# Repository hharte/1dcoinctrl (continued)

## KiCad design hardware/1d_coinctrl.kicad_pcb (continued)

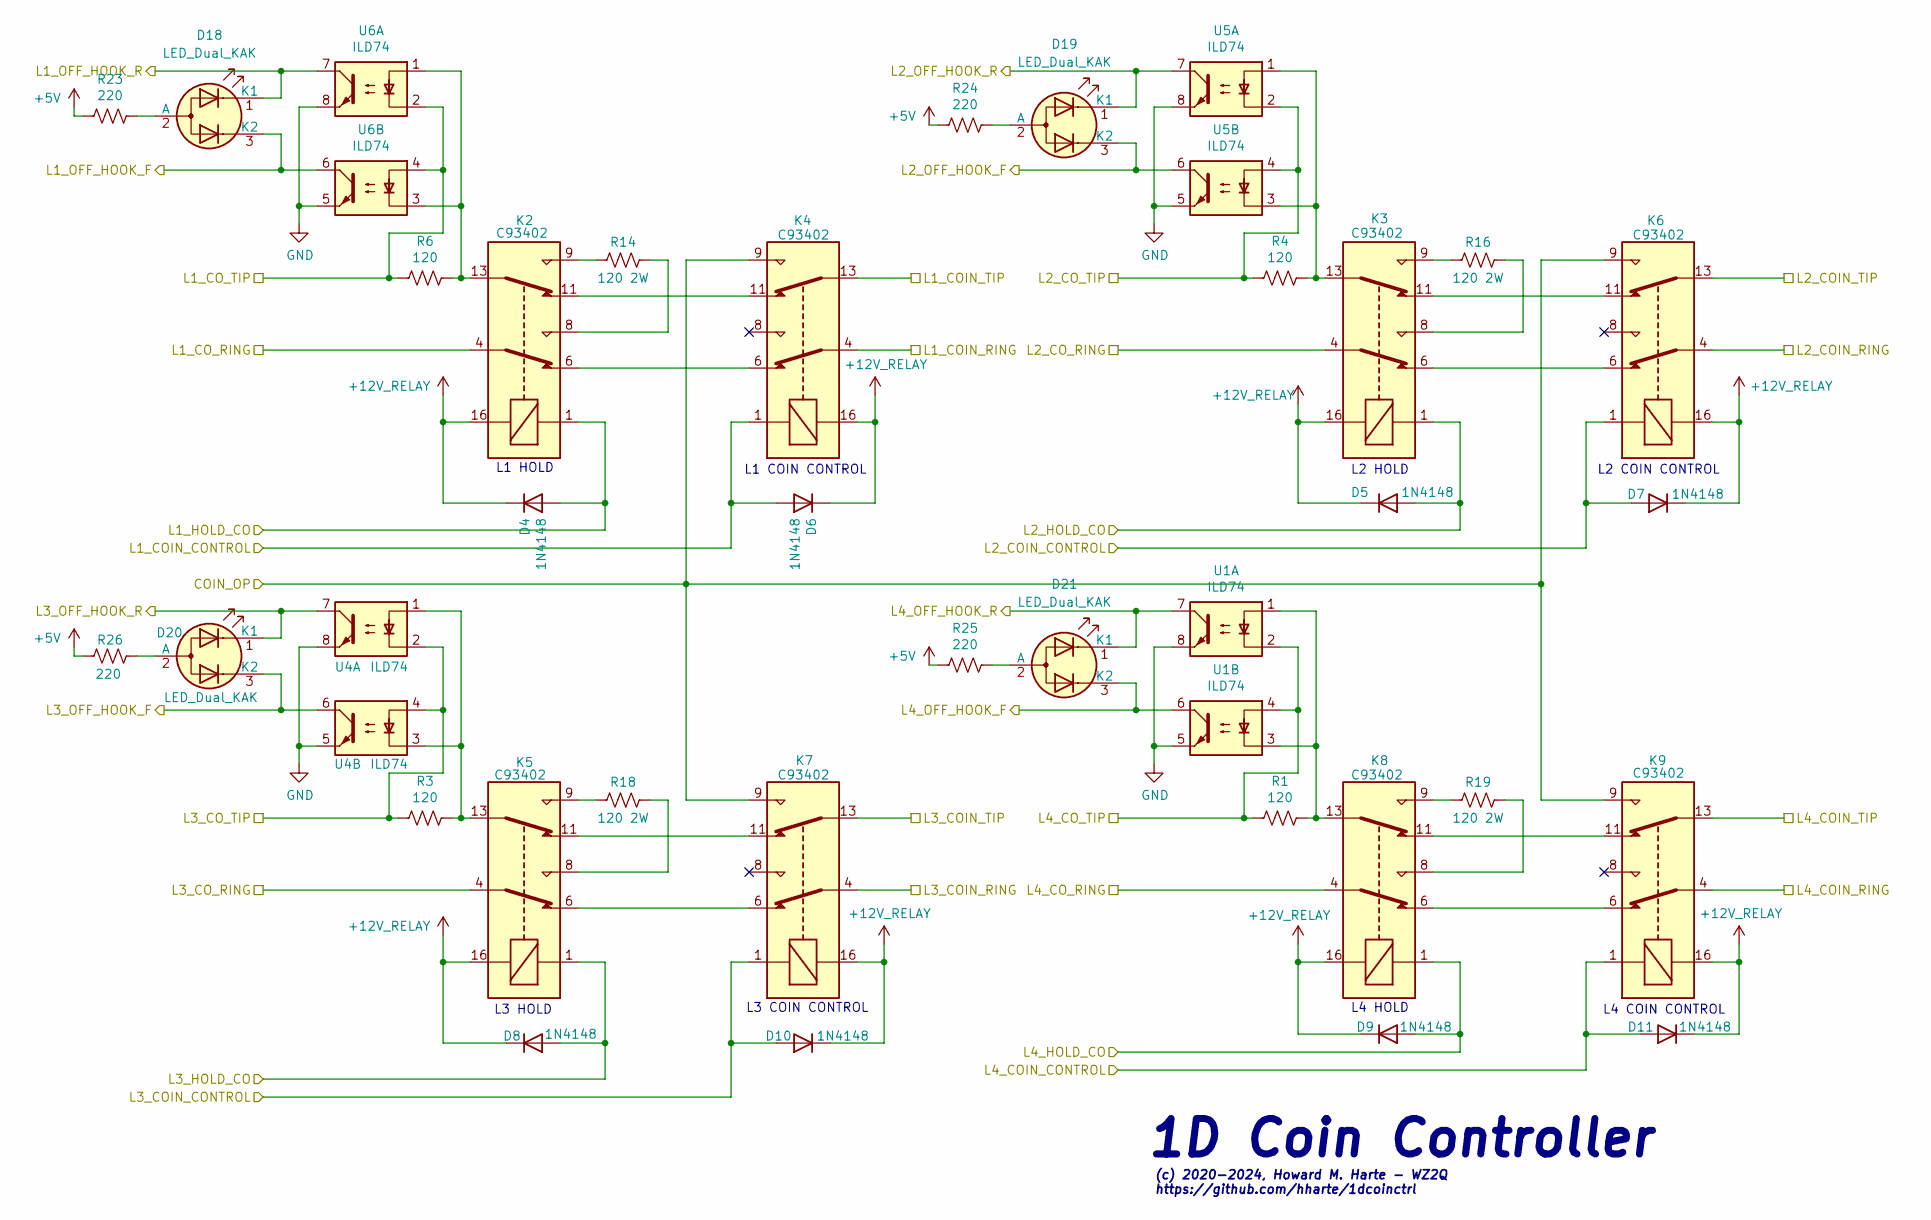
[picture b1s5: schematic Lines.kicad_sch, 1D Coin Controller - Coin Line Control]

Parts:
D4, D5, D6, D7, D8, D9, D10, D11: 1N4148; D_DO-35_SOD27_P7.62mm_Horizontal; MPN 1N4148TA; Digi-Key_PN 1N4148TACT-ND
D18, D19, D20, D21: LED_Dual_KAK; LED_D5.0mm-3; MPN XLMDKVG59MCA; Digi-Key_PN 1497-1357-ND
K2, K3, K4, K5, K6, K7, K8, K9: C93402; Relay_DPDT_Omron_G5V-2; MPN C93402; Digi-Key_PN PB1125-ND
R1, R3, R4, R6: 120; R_Axial_DIN0207_L6.3mm_D2.5mm_P7.62mm_Horizontal; MPN CFM12JT120R; Digi-Key_PN S120HCT-ND
R14, R16, R18, R19: 120 2W; R_Axial_DIN0516_L15.5mm_D5.0mm_P20.32mm_Horizontal; MPN FMP200JR-52-120R; Digi-Key_PN 120ZCT-ND
R23, R24, R25, R26: 220; R_Axial_DIN0207_L6.3mm_D2.5mm_P7.62mm_Horizontal; MPN CFM12JT220R; Digi-Key_PN S220HCT-ND
U1, U4, U5, U6: ILD74; DIP-8_W7.62mm_Socket; MPN CNY74-2H; Digi-Key_PN CNY74-2H-ND

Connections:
+5V: R23.2, R24.2, R25.2, R26.2; also elsewhere on the board
+12V_RELAY: D4.1 (K), D5.1 (K), D6.1 (K), D7.1 (K), D8.1 (K), D9.1 (K), D10.1 (K), D11.1 (K), K2.16, K3.16, K4.16, K5.16, K6.16, K7.16, K8.16, K9.16; also elsewhere on the board
/Coin Line Control/COIN_OP: K4.9, K6.9, K7.9, K9.9; also elsewhere on the board
/Coin Line Control/L1_COIN_CONTROL: D6.2 (A), K4.1; also elsewhere on the board
/Coin Line Control/L1_HOLD_CO: D4.2 (A), K2.1; also elsewhere on the board
/Coin Line Control/L1_OFF_HOOK_F: D18.3 (K2), U6.6; also elsewhere on the board
/Coin Line Control/L1_OFF_HOOK_R: D18.1 (K1), U6.7; also elsewhere on the board
/Coin Line Control/L2_COIN_CONTROL: D7.2 (A), K6.1; also elsewhere on the board
/Coin Line Control/L2_HOLD_CO: D5.2 (A), K3.1; also elsewhere on the board
/Coin Line Control/L2_OFF_HOOK_F: D19.3 (K2), U5.6; also elsewhere on the board
/Coin Line Control/L2_OFF_HOOK_R: D19.1 (K1), U5.7; also elsewhere on the board
/Coin Line Control/L3_COIN_CONTROL: D10.2 (A), K7.1; also elsewhere on the board
/Coin Line Control/L3_HOLD_CO: D8.2 (A), K5.1; also elsewhere on the board
/Coin Line Control/L3_OFF_HOOK_F: D20.3 (K2), U4.6; also elsewhere on the board
/Coin Line Control/L3_OFF_HOOK_R: D20.1 (K1), U4.7; also elsewhere on the board
/Coin Line Control/L4_COIN_CONTROL: D11.2 (A), K9.1; also elsewhere on the board
/Coin Line Control/L4_HOLD_CO: D9.2 (A), K8.1; also elsewhere on the board
/Coin Line Control/L4_OFF_HOOK_F: D21.3 (K2), U1.6; also elsewhere on the board
/Coin Line Control/L4_OFF_HOOK_R: D21.1 (K1), U1.7; also elsewhere on the board
/L1_COIN_RING: K4.4; also elsewhere on the board
/L1_COIN_TIP: K4.13; also elsewhere on the board
/L1_CO_RING: K2.4; also elsewhere on the board
/L1_CO_TIP: R6.2, U6.2, U6.4; also elsewhere on the board
/L2_COIN_RING: K6.4; also elsewhere on the board
/L2_COIN_TIP: K6.13; also elsewhere on the board
/L2_CO_RING: K3.4; also elsewhere on the board
/L2_CO_TIP: R4.2, U5.2, U5.4; also elsewhere on the board
/L3_COIN_RING: K7.4; also elsewhere on the board
/L3_COIN_TIP: K7.13; also elsewhere on the board
/L3_CO_RING: K5.4; also elsewhere on the board
/L3_CO_TIP: R3.2, U4.2, U4.4; also elsewhere on the board
/L4_COIN_RING: K9.4; also elsewhere on the board
/L4_COIN_TIP: K9.13; also elsewhere on the board
/L4_CO_RING: K8.4; also elsewhere on the board
/L4_CO_TIP: R1.2, U1.2, U1.4; also elsewhere on the board
GND: U1.5, U1.8, U4.5, U4.8, U5.5, U5.8, U6.5, U6.8; also elsewhere on the board
unnamed: D18.2 (A), R23.1
unnamed: D19.2 (A), R24.1
unnamed: D20.2 (A), R26.1
unnamed: D21.2 (A), R25.1
unnamed: K2.6, K4.6
unnamed: K2.8, R14.1
unnamed: K2.9, R14.2
unnamed: K2.11, K4.11
unnamed: K2.13, R6.1, U6.1, U6.3
unnamed: K3.6, K6.6
unnamed: K3.8, R16.1
unnamed: K3.9, R16.2
unnamed: K3.11, K6.11
unnamed: K3.13, R4.1, U5.1, U5.3
unnamed: K5.6, K7.6
unnamed: K5.8, R18.1
unnamed: K5.9, R18.2
unnamed: K5.11, K7.11
unnamed: K5.13, R3.1, U4.1, U4.3
unnamed: K8.6, K9.6
unnamed: K8.8, R19.1
unnamed: K8.9, R19.2
unnamed: K8.11, K9.11
unnamed: K8.13, R1.1, U1.1, U1.3

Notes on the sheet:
L2 HOLD
L4 COIN CONTROL
L1 COIN CONTROL
L2 COIN CONTROL
L3 HOLD
1D Coin Controller
L1 HOLD
L3 COIN CONTROL
L4 HOLD
(c) 2020-2024, Howard M. Harte - WZ2Q https://github.com/hharte/1dcoinctrl

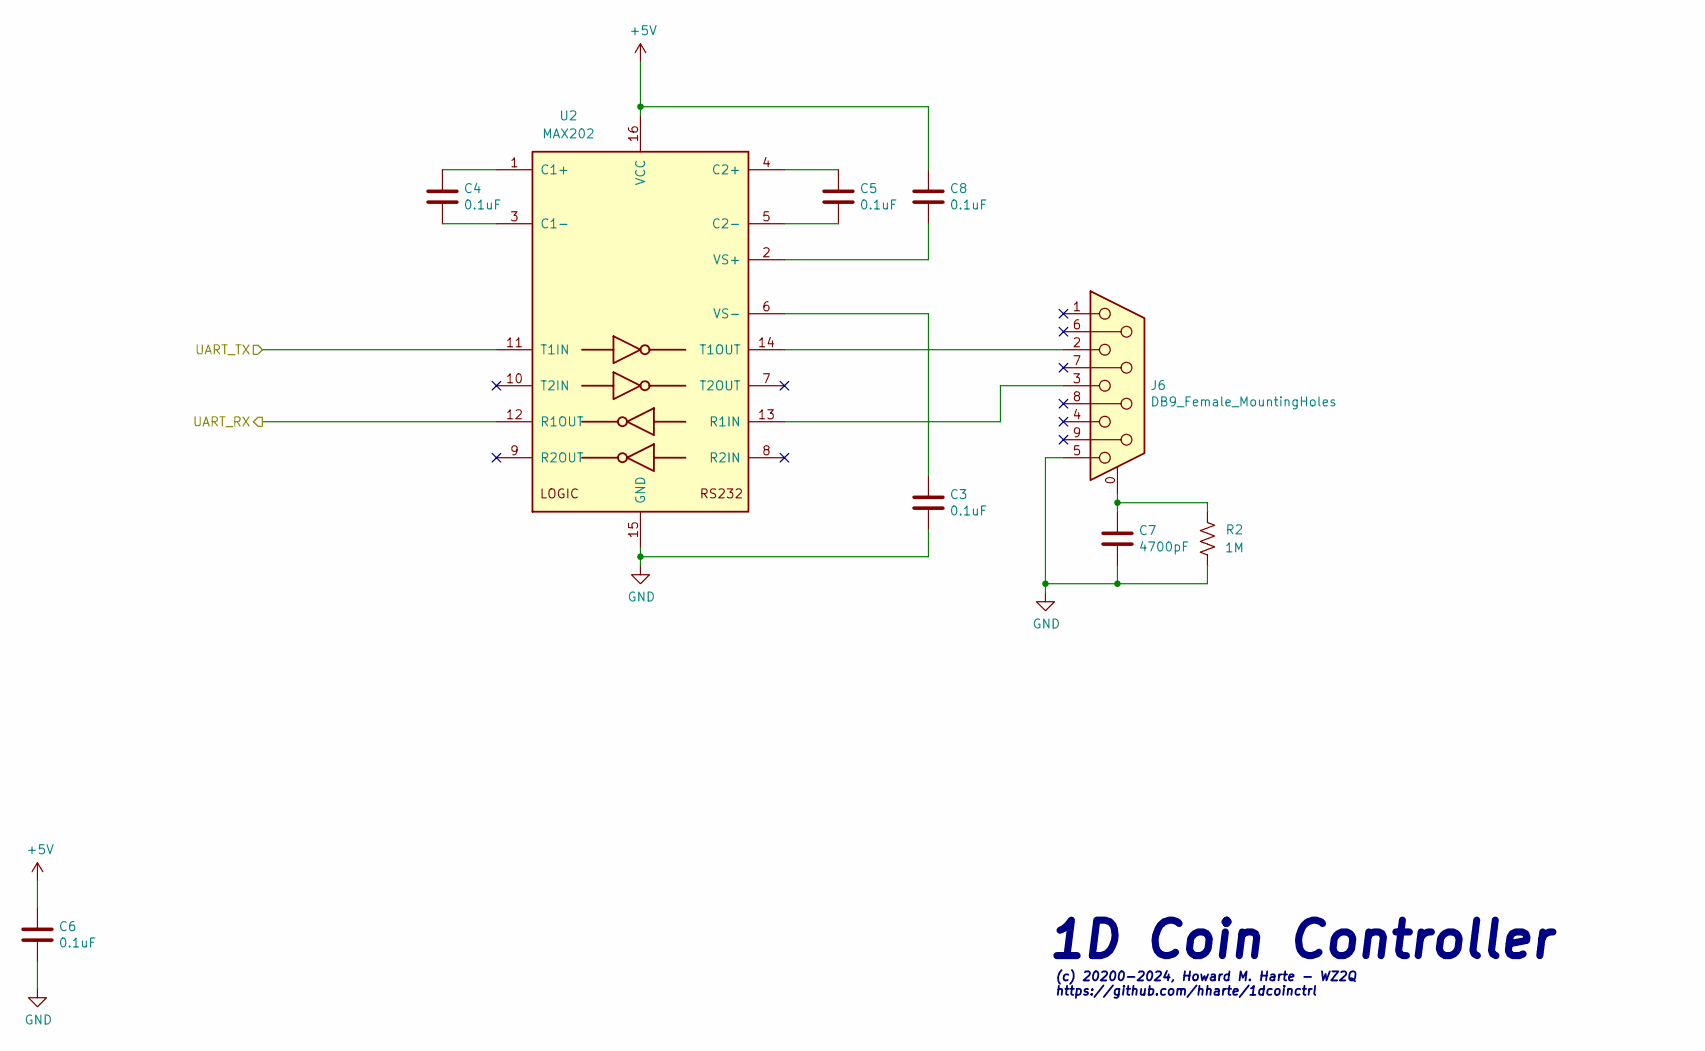
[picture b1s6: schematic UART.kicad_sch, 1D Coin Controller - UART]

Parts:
C3, C4, C5, C6, C8: 0.1uF; C_Disc_D3.0mm_W2.0mm_P2.50mm; MPN K104M15X7RF5TL2; Digi-Key_PN 56-K104M15X7RF5TL2CT-ND
C7: 4700pF; C_Disc_D4.3mm_W1.9mm_P5.00mm; MPN S472M39Z5UN63J5R; Digi-Key_PN 1288PH-ND
J6: DB9_Female_MountingHoles; DSUB-9_Female_Horizontal_P2.77x2.84mm_EdgePinOffset7.70mm_H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; MPN 747844-4; Digi-Key_PN A23303-ND
R2: 1M; R_Axial_DIN0207_L6.3mm_D2.5mm_P7.62mm_Horizontal; MPN CFM12JT1M00; Digi-Key_PN S1MHCT-ND
U2: MAX202; DIP-16_W7.62mm; MPN HIN232CPZ; Digi-Key_PN HIN232CPZ-ND

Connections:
+5V: C6.1, C8.1, U2.16 (VCC); also elsewhere on the board
/GPIO/RS232_RXD: U2.12 (R1OUT); also elsewhere on the board
/GPIO/RS232_TXD: U2.11 (T1IN); also elsewhere on the board
GND: C3.2, C6.2, C7.2, J6.5, R2.2, U2.15 (GND); also elsewhere on the board
unnamed: C7.1, J6.0 (PAD), R2.1
unnamed: C4.1, U2.1 (C1+)
unnamed: C4.2, U2.3 (C1-)
unnamed: C5.1, U2.4 (C2+)
unnamed: C5.2, U2.5 (C2-)
unnamed: J6.3, U2.13 (R1IN)
unnamed: J6.2, U2.14 (T1OUT)
unnamed: C8.2, U2.2 (VS+)
unnamed: C3.1, U2.6 (VS-)

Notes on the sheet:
(c) 20200-2024, Howard M. Harte - WZ2Q https://github.com/hharte/1dcoinctrl
1D Coin Controller

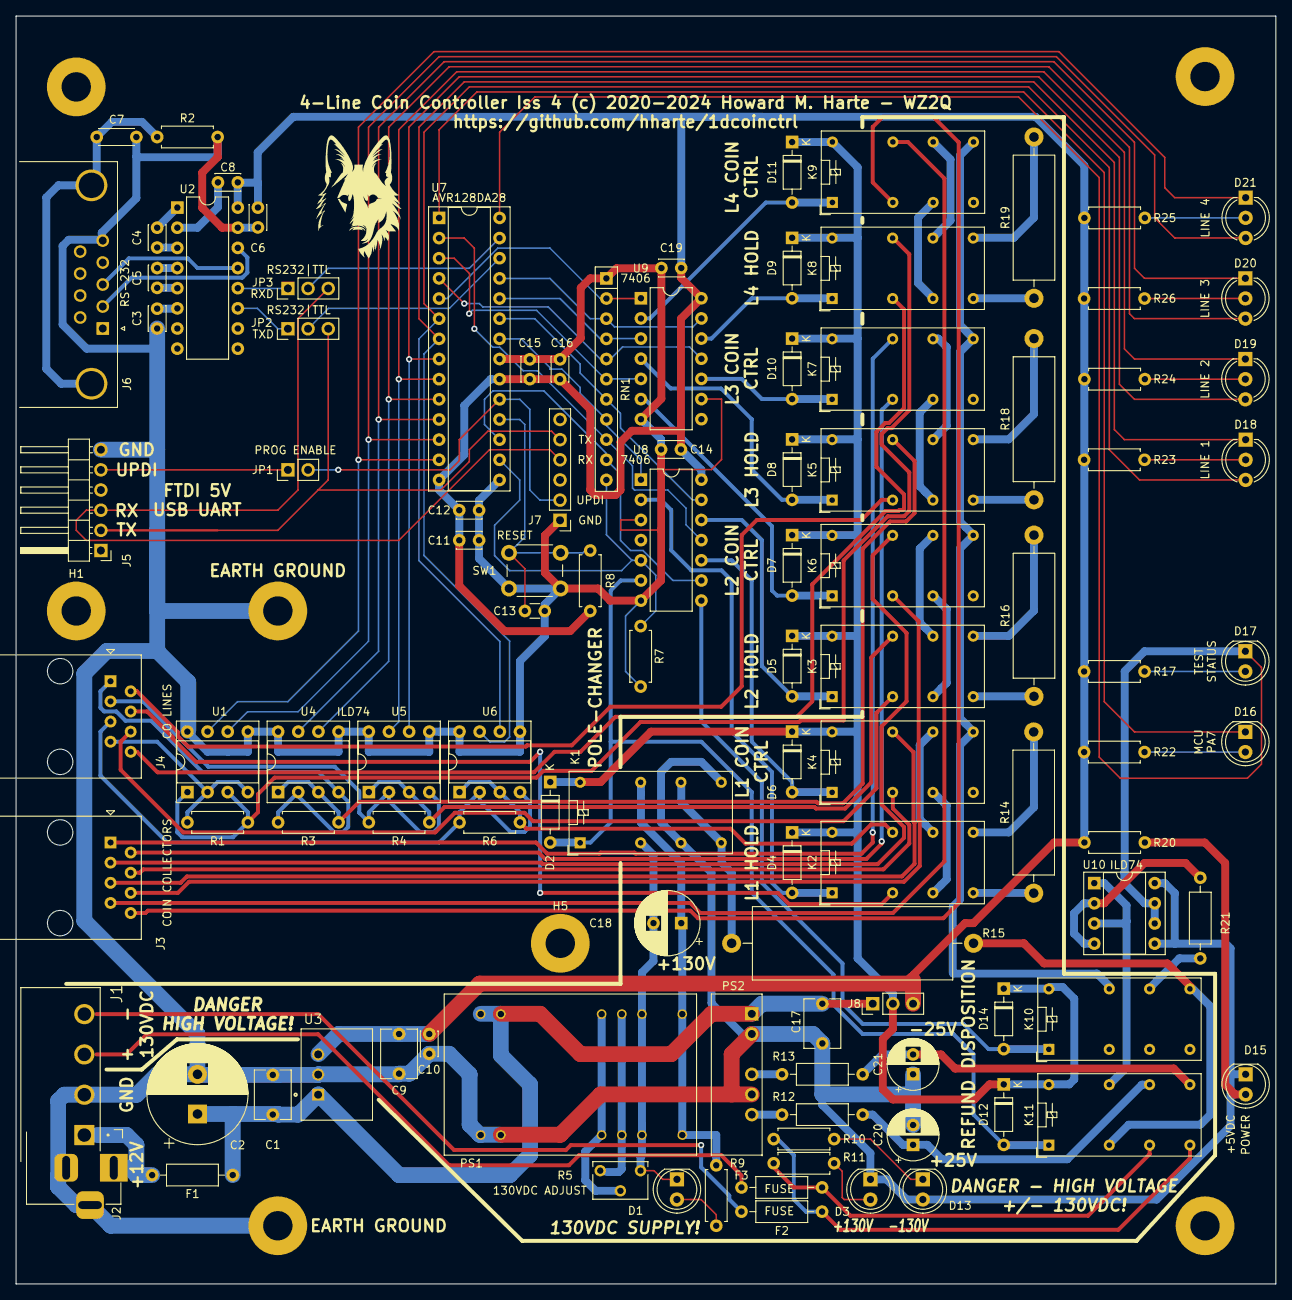
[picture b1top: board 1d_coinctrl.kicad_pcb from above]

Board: 2 copper layers, 158.8 x 159.8 mm, 115 parts (0 on the bottom side), 117 nets.

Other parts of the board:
Deena: LOGO; Deena

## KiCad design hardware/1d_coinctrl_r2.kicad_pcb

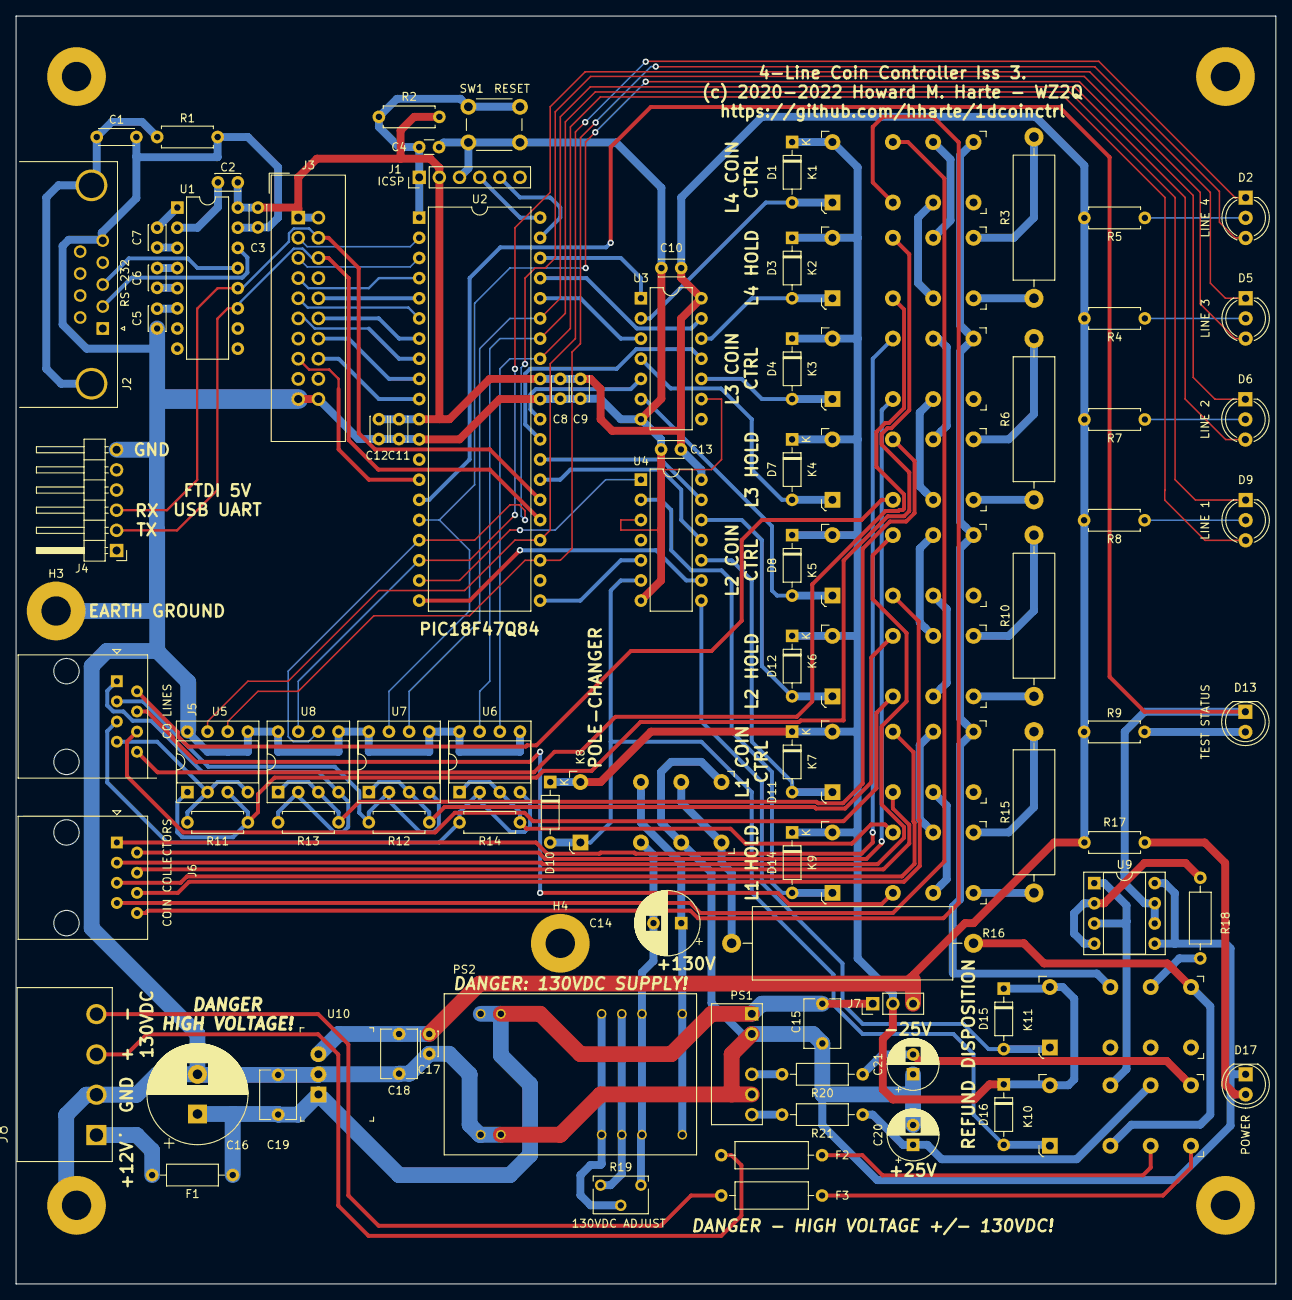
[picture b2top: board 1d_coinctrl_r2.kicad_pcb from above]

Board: 2 copper layers, 158.8 x 159.8 mm, 100 parts (0 on the bottom side), 118 nets.

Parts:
C1: 4700pF; C_Disc_D4.3mm_W1.9mm_P5.00mm
C2, C3, C5, C6, C7, C8, C10, C11, C13, C17: 0.1uF; C_Disc_D3.0mm_W2.0mm_P2.50mm
C4: 0.01uF; C_Disc_D3.0mm_W1.6mm_P2.50mm
C9, C12: 0.001uF; C_Disc_D3.0mm_W2.0mm_P2.50mm
C14: 4.7uF 250V; CP_Radial_D8.0mm_P3.50mm
C15, C19: 10uF 25V; C_Disc_D6.0mm_W4.4mm_P5.00mm
C16: 1000uF 25V; CP_Radial_D12.5mm_P5.00mm
C18: 22uF 16V; C_Disc_D6.0mm_W4.4mm_P5.00mm
C20, C21: 10uF 50V; CP_Radial_D6.3mm_P2.50mm
D1, D3, D4, D7, D8, D10, D11, D12, D14, D15, D16: 1N4148; D_DO-35_SOD27_P7.62mm_Horizontal
D2, D5, D6, D9: LED_Dual_KAK; LED_D5.0mm-3
D13: LED; LED_D5.0mm
D17: POWER_LED; LED_D5.0mm
F1: Fuse; R_Axial_DIN0207_L6.3mm_D2.5mm_P10.16mm_Horizontal
F2, F3: Fuse 100mA; R_Axial_DIN0309_L9.0mm_D3.2mm_P12.70mm_Horizontal
H1, H2, H4, H6: MountingHole; MountingHole_3.7mm_Pad
H3, H5: MountingHole_Pad; MountingHole_3.7mm_Pad
J1: Conn_01x06_Male; PinHeader_1x06_P2.54mm_Vertical
J2: DB9_Female_MountingHoles; DSUB-9_Female_Horizontal_P2.77x2.84mm_EdgePinOffset7.70mm_H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
J3: Conn_02x10_Odd_Even; IDC-Header_2x10_P2.54mm_Vertical
J4: Conn_01x06_Male; PinHeader_1x06_P2.54mm_Horizontal
J5: CO LINE; RJ45_Amphenol_54602-x08_Horizontal
J6: COIN LINE; RJ45_Amphenol_54602-x08_Horizontal
J7: V_RLY_SEL; PinHeader_1x03_P2.54mm_Vertical
J8: TBP01R1-508-04BE; CUI_TBP01R1-508-04BE
K1: L4_COIN_CTRL; Relay_THT_G5V-2
K2: L4_HOLD; Relay_THT_G5V-2
K3: L3_COIN_CTRL; Relay_THT_G5V-2
K4: L3_HOLD; Relay_THT_G5V-2
K5: L2_COIN_CTRL; Relay_THT_G5V-2
K6: L2_HOLD; Relay_THT_G5V-2
K7: L1_COIN_CTRL; Relay_THT_G5V-2
K8, K10, K11: G5V-2-DC12; Relay_THT_G5V-2
K9: L1_HOLD; Relay_THT_G5V-2
PS1: IA1224S
PS2: R12-100B; CONV_R12-100B
R1: 1M; R_Axial_DIN0207_L6.3mm_D2.5mm_P7.62mm_Horizontal
R2: 10K; R_Axial_DIN0207_L6.3mm_D2.5mm_P7.62mm_Horizontal
R3, R6, R10, R15: 120 2W; R_Axial_DIN0516_L15.5mm_D5.0mm_P20.32mm_Horizontal
R4, R5, R7, R8, R9, R17: 220; R_Axial_DIN0207_L6.3mm_D2.5mm_P7.62mm_Horizontal
R11, R12, R13, R14: 120; R_Axial_DIN0207_L6.3mm_D2.5mm_P7.62mm_Horizontal
R16: 1.5K 5W; R_Axial_Power_L25.0mm_W9.0mm_P30.48mm
R18, R20, R21: 1.5K 1W; R_Axial_DIN0207_L6.3mm_D2.5mm_P10.16mm_Horizontal
R19: 5K; Potentiometer_Bourns_3266W_Vertical
SW1: SW_Push; SW_PUSH_6mm
U1: MAX202; DIP-16_W7.62mm
U2: PIC18F47Q84-IP; DIP-40_W15.24mm
U3, U4: 74LS06; DIP-14_W7.62mm
U5, U6, U7, U8, U9: ILD74; DIP-8_W7.62mm_Socket
U10: V7805-1000; 3-SIP_Module_V7805-1000

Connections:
+5V: C2.1, C3.1, C8.1, C9.1, C10.1, C11.1, C12.1, C13.1, C17.1, C18.1, J1.2, J3.1, J3.2, J7.3, R2.1, R4.2, R5.2, R7.2, R8.2, R9.1, R17.2, U1.16 (VCC), U2.11 (VDD), U2.32 (VDD), U3.14 (VCC), U4.14 (VCC), U10.3 (Vo+)
+12V: C15.1, C16.1, C19.1, F1.1, J7.1, PS1.1 (Vin+), PS2.22 (+VIN), PS2.23 (+VIN), U10.1 (Vin+)
+12V_RELAY: D1.1 (K), D3.1 (K), D4.1 (K), D7.1 (K), D8.1 (K), D10.1 (K), D11.1 (K), D12.1 (K), D14.1 (K), D15.1 (K), D16.1 (K), J7.2, K1.16 (COIL), K2.16 (COIL), K3.16 (COIL), K4.16 (COIL), K5.16 (COIL), K6.16 (COIL), K7.16 (COIL), K8.16 (COIL), K9.16 (COIL), K10.16 (COIL), K11.16 (COIL)
/12VIN: F1.2, J8.1
/Coin Line Control/COIN_OP: K1.9 (NO2), K3.9 (NO2), K5.9 (NO2), K7.9 (NO2), K11.13 (COM2)
/Coin Line Control/L1_COIN_CONTROL: D11.2 (A), K7.1 (COIL), U4.10
/Coin Line Control/L1_HOLD_CO: D14.2 (A), K9.1 (COIL), U4.2
/Coin Line Control/L1_OFF_HOOK_F: D9.3 (K2), U2.33 (RB0/AN12/INT0/FLT0/SDI/SDA), U6.6
/Coin Line Control/L1_OFF_HOOK_R: D9.1 (K1), U2.34 (RB1/AN10/INT1/SCK/SCL), U6.7
/Coin Line Control/L2_COIN_CONTROL: D8.2 (A), K5.1 (COIL), U3.6
/Coin Line Control/L2_HOLD_CO: D12.2 (A), K6.1 (COIL), U4.12
/Coin Line Control/L2_OFF_HOOK_F: D6.3 (K2), U2.35 (RB2/AN8/INT2/VMO), U7.6
/Coin Line Control/L3_COIN_CONTROL: D4.2 (A), K3.1 (COIL), U3.10
/Coin Line Control/L3_HOLD_CO: D7.2 (A), K4.1 (COIL), U3.4
/Coin Line Control/L4_COIN_CONTROL: D1.2 (A), K1.1 (COIL), U3.2
/Coin Line Control/L4_HOLD_CO: D3.2 (A), K2.1 (COIL), U3.12
/Common Control/+130VDC: F2.1, K10.6 (NC1)
/Common Control/-130VDC: F3.1, K10.8 (NO1)
/Common Control/DISPOSITION: D15.2 (A), K11.1 (COIL), U4.8
/Common Control/REFUND: D10.2 (A), D16.2 (A), K8.1 (COIL), K10.1 (COIL), U4.6
/Common Control/TEST_STATUS_N: D13.1 (K), U2.15 (T1OSO/T13CKI/RC0), U9.6, U9.7
/Common Control/V_COIN_RELAY: K10.4 (COM1), K11.9 (NO2), R16.1
/GPIO/C1IN+: J3.10, U2.5 (RA3/AN3/Vref+)
/GPIO/C1OUT: J3.12, U2.7 (RA5/AN4/~SS/HLVDIN/C2OUT)
/GPIO/C2IN+: J3.7, U2.4 (RA2/AN2/Vref-/CVref)
/GPIO/C2OUT: J3.9, U2.6 (RA4/T0CKI/C1OUT/RCV)
/GPIO/C12IN0-: J3.3, U2.2 (RA0/AN0)
/GPIO/C12IN1-: J3.5, U2.3 (RA1/AN1)
/GPIO/ICSP_PGC: J1.5, U2.39 (RB6/KBI2/PGC)
/GPIO/ICSP_PGD: J1.4, U2.40 (RB7/KBI3/PGD)
/GPIO/L2_OFF_HOOK_R: D6.1 (K1), U2.16 (~UOE/CCP2/T1OSI/RC1), U7.7
/GPIO/L3_OFF_HOOK_F: D5.3 (K2), U2.17 (P1A/CCP1/RC2), U8.6
/GPIO/L3_OFF_HOOK_R: D5.1 (K1), U2.18 (RC3), U8.7
/GPIO/L4_OFF_HOOK_F: D2.3 (K2), U2.23 (VM/RC4), U5.6
/GPIO/L4_OFF_HOOK_R: D2.1 (K1), U2.24 (VP/RC5), U5.7
/GPIO/MCLR: C4.1, J1.1, R2.2, SW1.1, U2.1 (Vpp/~MCLR/RE3)
/GPIO/RA6_CLKO: J3.15, U2.14 (RA6/OSC2/CLKO)
/GPIO/RB1_L4_COIN_CONTROL: U2.38 (RB5/KBI1/PGM), U3.1
/GPIO/RB3_L3_HOLD_CO: U2.36 (RB3/AN9/CCP2/VPO), U3.3
/GPIO/RB4_L4_HOLD_CO: U2.37 (RB4/AN11/KBI0/CSSPP), U3.13
/GPIO/RD0_L1_HOLD_CD: U2.19 (SPP0/RD0), U4.1
/GPIO/RD1_DISPOSITION: U2.20 (SPP1/RD1), U4.9
/GPIO/RD2_REFUND: U2.21 (SPP2/RD2), U4.5
/GPIO/RD4_L1_COIN_CONTROL: U2.27 (SPP4/RD4), U4.11
/GPIO/RD5_L2_HOLD_CO: U2.28 (P1B/SPP5/RD5), U4.13
/GPIO/RD6_L3_COIN_CONTROL: U2.29 (P1C/SPP6/RD6), U3.11
/GPIO/RD7_L2_COIN_CONTROL: U2.30 (P1D/SPP7/RD7), U3.5
/GPIO/RE0: J3.11, U2.8 (CK1SPP/AN5/RE0)
/GPIO/RE1: J3.14, U2.9 (CK2SPP/AN6/RE1)
/GPIO/RE2: J3.16, U2.10 (OESPP/AN7/RE2)
/GPIO/UART_RX: J3.4, J4.3, U1.12 (R1OUT), U2.26 (SDO/RX/DT/RC7)
/GPIO/UART_TX: J3.6, J4.2, U1.11 (T1IN), U2.25 (TX/CK/RC6)
/L1_COIN_RING: J6.4, K7.4 (COM1)
/L1_COIN_TIP: J6.5, K7.13 (COM2)
/L1_CO_RING: J5.4, K9.4 (COM1)
/L1_CO_TIP: J5.5, R14.2, U6.2, U6.4
/L2_COIN_RING: J6.6, K5.4 (COM1)
/L2_COIN_TIP: J6.3, K5.13 (COM2)
/L2_CO_RING: J5.6, K6.4 (COM1)
/L2_CO_TIP: J5.3, R12.2, U7.2, U7.4
/L3_COIN_RING: J6.2, K3.4 (COM1)
/L3_COIN_TIP: J6.1, K3.13 (COM2)
/L3_CO_RING: J5.2, K4.4 (COM1)
/L3_CO_TIP: J5.1, R13.2, U8.2, U8.4
/L4_COIN_RING: J6.8, K1.4 (COM1)
/L4_COIN_TIP: J6.7, K1.13 (COM2)
/L4_CO_RING: J5.8, K2.4 (COM1)
/L4_CO_TIP: J5.7, R11.2, U5.2, U5.4
/Power/+25VDC: C20.1, K10.11 (NC2), R21.1
/Power/+130VDC: C14.1, K8.13 (COM2), PS2.12 (+VOUT), PS2.13 (+VOUT)
/Power/-25VDC: C21.2, K10.9 (NO2), R20.1
/Power/-130VDC: C14.2, K8.4 (COM1), PS2.10 (-VOUT), PS2.15 (-VOUT), R19.1
GND: C1.2, C3.2, C4.2, C5.2, C8.2, C9.2, C10.2, C11.2, C12.2, C13.2, C15.2, C16.2, C17.2, C18.2, C19.2, C20.2, C21.1, D17.1 (K), H3.1, H5.1, J1.3, J2.5, J3.19, J3.20, J4.6, J8.2, K8.6 (NC1), K8.9 (NO2), PS1.2 (Vin-), PS1.4 (GND), PS2.2 (-VIN), PS2.3 (-VIN), R1.2, SW1.2, U1.15 (GND), U2.12 (VSS), U2.31 (VSS), U3.7 (GND), U3.9, U4.3, U4.7 (GND), U5.5, U5.8, U6.5, U6.8, U7.5, U7.8, U8.5, U8.8, U9.5, U9.8, U10.2 (GND)
unnamed: C1.1, J2.0 (PAD), R1.1
unnamed: C2.2, U1.2 (VS+)
unnamed: C5.1, U1.6 (VS-)
unnamed: C6.1, U1.4 (C2+)
unnamed: C6.2, U1.5 (C2-)
unnamed: C7.1, U1.1 (C1+)
unnamed: C7.2, U1.3 (C1-)
unnamed: D2.2 (A), R5.1
unnamed: D5.2 (A), R4.1
unnamed: D6.2 (A), R7.1
unnamed: D9.2 (A), R8.1
unnamed: D13.2 (A), R9.2
unnamed: D17.2 (A), R17.1
unnamed: F2.2, J8.3
unnamed: F3.2, J8.4
unnamed: J2.2, U1.14 (T1OUT)
unnamed: J2.3, U1.13 (R1IN)
unnamed: K1.6 (NC1), K2.6 (NC1)
unnamed: K1.11 (NC2), K2.11 (NC2)
unnamed: K2.8 (NO1), R3.1
unnamed: K2.9 (NO2), R3.2
unnamed: K2.13 (COM2), R11.1, U5.1, U5.3
unnamed: K3.6 (NC1), K4.6 (NC1)
unnamed: K3.11 (NC2), K4.11 (NC2)
unnamed: K4.8 (NO1), R6.1
unnamed: K4.9 (NO2), R6.2
unnamed: K4.13 (COM2), R13.1, U8.1, U8.3
unnamed: K5.6 (NC1), K6.6 (NC1)
unnamed: K5.11 (NC2), K6.11 (NC2)
unnamed: K6.8 (NO1), R10.1
unnamed: K6.9 (NO2), R10.2
unnamed: K6.13 (COM2), R12.1, U7.1, U7.3
unnamed: K7.6 (NC1), K9.6 (NC1)
unnamed: K7.11 (NC2), K9.11 (NC2)
unnamed: K8.8 (NO1), K8.11 (NC2), R16.2
unnamed: K9.8 (NO1), R15.1
unnamed: K9.9 (NO2), R15.2
unnamed: K9.13 (COM2), R14.1, U6.1, U6.3
unnamed: K10.13 (COM2), U9.1, U9.3
unnamed: K11.11 (NC2), R18.1
unnamed: PS1.3 (Vout-), R20.2
unnamed: PS1.5 (Vout+), R21.2
unnamed: PS2.9 (VREF), PS2.16 (VREF), R19.3
unnamed: PS2.8 (VADJ), PS2.17 (VADJ), R19.2
unnamed: R18.2, U9.2, U9.4

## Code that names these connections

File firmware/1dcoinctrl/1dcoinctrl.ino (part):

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 */

/* Port A */
#define L1_HOLD_CO          0   /* PA0 L1_HOLD_CO */
#define L2_HOLD_CO          1   /* PA1 L2_HOLD_CO */
#define L3_HOLD_CO          2   /* PA2 L3_HOLD_CO */
#define L4_HOLD_CO          3   /* PA3 L4_HOLD_CO */
//#define UART_TXD          4   /* PA4 UART TXD */
//#define UART_RXD          5   /* PA5 UART RXD */
#define TEST_STATUS_IN      6   /* PA6 */
#define STATUS_LED          7   /* PA7 */
#define STATUS_LED_B        (1 << 7)  /* PA7 */

/* Port C */
#define L1_COIN_CONTROL     8   /* PC0 */
#define L2_COIN_CONTROL     9   /* PC1 */
#define L3_COIN_CONTROL     10  /* PC2 */
#define L4_COIN_CONTROL     11  /* PC3 */

/* Port D: Hook State Inputs */
#define L1_OFF_HOOK_F       12  /* PD0 */
#define L1_OFF_HOOK_R       13  /* PD1 */
#define L2_OFF_HOOK_F       14  /* PD2 */
#define L2_OFF_HOOK_R       15  /* PD3 */
#define L3_OFF_HOOK_F       16  /* PD4 */
#define L3_OFF_HOOK_R       17  /* PD5 */
#define L4_OFF_HOOK_F       18  /* PD6 */
#define L4_OFF_HOOK_R       19  /* PD7 */

/* Port F: REFUND and DISPOSITION relay control. */
#define REFUND              20  /* PF0 */
#define DISPOSITION         21  /* PF1 */

#define LED_ON(x)           VPORTA.OUT &= ~STATUS_LED_B;
#define LED_OFF(x)          VPORTA.OUT |=  STATUS_LED_B;
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#define OFF_HOOK_F          (1)
#define OFF_HOOK_R          (2)

#define REFUND_ON           digitalWrite(REFUND, HIGH)
#define REFUND_OFF          digitalWrite(REFUND, LOW)
#define DISPOSITION_ON      digitalWrite(DISPOSITION, HIGH)
#define DISPOSITION_OFF     digitalWrite(DISPOSITION, LOW)
#define L1_HOLD_ON          digitalWrite(L1_HOLD_CO, HIGH)
#define L1_HOLD_OFF         digitalWrite(L1_HOLD_CO, LOW)
#define L2_HOLD_ON          digitalWrite(L2_HOLD_CO, HIGH)
#define L2_HOLD_OFF         digitalWrite(L2_HOLD_CO, LOW)
#define L3_HOLD_ON          digitalWrite(L3_HOLD_CO, HIGH)
#define L3_HOLD_OFF         digitalWrite(L3_HOLD_CO, LOW)
#define L4_HOLD_ON          digitalWrite(L4_HOLD_CO, HIGH)
#define L4_HOLD_OFF         digitalWrite(L4_HOLD_CO, LOW)

#define L1_COIN_CTRL_ON     digitalWrite(L1_COIN_CONTROL, HIGH)
#define L1_COIN_CTRL_OFF    digitalWrite(L1_COIN_CONTROL, LOW)
#define L2_COIN_CTRL_ON     digitalWrite(L2_COIN_CONTROL, HIGH)
#define L2_COIN_CTRL_OFF    digitalWrite(L2_COIN_CONTROL, LOW)
#define L3_COIN_CTRL_ON     digitalWrite(L3_COIN_CONTROL, HIGH)
#define L3_COIN_CTRL_OFF    digitalWrite(L3_COIN_CONTROL, LOW)
#define L4_COIN_CTRL_ON     digitalWrite(L4_COIN_CONTROL, HIGH)
#define L4_COIN_CTRL_OFF    digitalWrite(L4_COIN_CONTROL, LOW)

#define TEST_STATUS(x)      digitalRead(TEST_STATUS_IN)

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void setup(void) {

  /* Initialize serial port */
  Serial.swap(1); /* Use PA4/PA5 for UART */
  Serial.begin(BAUD_RATE);

  VPORTC.OUT = 0xFF;
  VPORTD.OUT = 0xFF;

  /* Initialize GPIO Pins */
  pinMode (L1_COIN_CONTROL, OUTPUT);
  pinMode (L2_COIN_CONTROL, OUTPUT);
  pinMode (L3_COIN_CONTROL, OUTPUT);
  pinMode (L4_COIN_CONTROL, OUTPUT);
  pinMode (L1_HOLD_CO,      OUTPUT);
  pinMode (L2_HOLD_CO,      OUTPUT);
  pinMode (L3_HOLD_CO,      OUTPUT);
  pinMode (L4_HOLD_CO,      OUTPUT);
  pinMode (STATUS_LED,      OUTPUT);
  pinMode (REFUND,          OUTPUT);
  pinMode (DISPOSITION,     OUTPUT);

  pinMode (TEST_STATUS_IN,  INPUT_PULLUP);
  pinMode (L1_OFF_HOOK_F,   INPUT_PULLUP);
  pinMode (L1_OFF_HOOK_R,   INPUT_PULLUP);
  pinMode (L2_OFF_HOOK_F,   INPUT_PULLUP);
  pinMode (L2_OFF_HOOK_R,   INPUT_PULLUP);
  pinMode (L3_OFF_HOOK_F,   INPUT_PULLUP);
  pinMode (L3_OFF_HOOK_R,   INPUT_PULLUP);
  pinMode (L4_OFF_HOOK_F,   INPUT_PULLUP);
  pinMode (L4_OFF_HOOK_R,   INPUT_PULLUP);

  takeOverTCA0();
  TCA0.SINGLE.CTRLB = TCA_SINGLE_WGMODE_NORMAL_gc;
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
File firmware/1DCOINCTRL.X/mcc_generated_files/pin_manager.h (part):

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// get/set L1_OFF_HOOK_F aliases
#define L1_OFF_HOOK_F_TRIS                 TRISBbits.TRISB0
#define L1_OFF_HOOK_F_LAT                  LATBbits.LATB0
#define L1_OFF_HOOK_F_PORT                 PORTBbits.RB0
#define L1_OFF_HOOK_F_WPU                  WPUBbits.WPUB0
#define L1_OFF_HOOK_F_OD                   ODCONBbits.ODCB0
#define L1_OFF_HOOK_F_ANS                  ANSELBbits.ANSELB0
#define L1_OFF_HOOK_F_SetHigh()            do { LATBbits.LATB0 = 1; } while(0)
#define L1_OFF_HOOK_F_SetLow()             do { LATBbits.LATB0 = 0; } while(0)
#define L1_OFF_HOOK_F_Toggle()             do { LATBbits.LATB0 = ~LATBbits.LATB0; } while(0)
#define L1_OFF_HOOK_F_GetValue()           PORTBbits.RB0
#define L1_OFF_HOOK_F_SetDigitalInput()    do { TRISBbits.TRISB0 = 1; } while(0)
#define L1_OFF_HOOK_F_SetDigitalOutput()   do { TRISBbits.TRISB0 = 0; } while(0)
#define L1_OFF_HOOK_F_SetPullup()          do { WPUBbits.WPUB0 = 1; } while(0)
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// get/set L1_OFF_HOOK_R aliases
#define L1_OFF_HOOK_R_TRIS                 TRISBbits.TRISB1
#define L1_OFF_HOOK_R_LAT                  LATBbits.LATB1
#define L1_OFF_HOOK_R_PORT                 PORTBbits.RB1
#define L1_OFF_HOOK_R_WPU                  WPUBbits.WPUB1
#define L1_OFF_HOOK_R_OD                   ODCONBbits.ODCB1
#define L1_OFF_HOOK_R_ANS                  ANSELBbits.ANSELB1
#define L1_OFF_HOOK_R_SetHigh()            do { LATBbits.LATB1 = 1; } while(0)
#define L1_OFF_HOOK_R_SetLow()             do { LATBbits.LATB1 = 0; } while(0)
#define L1_OFF_HOOK_R_Toggle()             do { LATBbits.LATB1 = ~LATBbits.LATB1; } while(0)
#define L1_OFF_HOOK_R_GetValue()           PORTBbits.RB1
#define L1_OFF_HOOK_R_SetDigitalInput()    do { TRISBbits.TRISB1 = 1; } while(0)
#define L1_OFF_HOOK_R_SetDigitalOutput()   do { TRISBbits.TRISB1 = 0; } while(0)
#define L1_OFF_HOOK_R_SetPullup()          do { WPUBbits.WPUB1 = 1; } while(0)
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// get/set IO_RB2 aliases
#define IO_RB2_TRIS                 TRISBbits.TRISB2
#define IO_RB2_LAT                  LATBbits.LATB2
#define IO_RB2_PORT                 PORTBbits.RB2
#define IO_RB2_WPU                  WPUBbits.WPUB2
#define IO_RB2_OD                   ODCONBbits.ODCB2
#define IO_RB2_ANS                  ANSELBbits.ANSELB2
#define IO_RB2_SetHigh()            do { LATBbits.LATB2 = 1; } while(0)
#define IO_RB2_SetLow()             do { LATBbits.LATB2 = 0; } while(0)
#define IO_RB2_Toggle()             do { LATBbits.LATB2 = ~LATBbits.LATB2; } while(0)
#define IO_RB2_GetValue()           PORTBbits.RB2
#define IO_RB2_SetDigitalInput()    do { TRISBbits.TRISB2 = 1; } while(0)
#define IO_RB2_SetDigitalOutput()   do { TRISBbits.TRISB2 = 0; } while(0)
#define IO_RB2_SetPullup()          do { WPUBbits.WPUB2 = 1; } while(0)
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// get/set L3_HOLD_CO aliases
#define L3_HOLD_CO_TRIS                 TRISBbits.TRISB3
#define L3_HOLD_CO_LAT                  LATBbits.LATB3
#define L3_HOLD_CO_PORT                 PORTBbits.RB3
#define L3_HOLD_CO_WPU                  WPUBbits.WPUB3
#define L3_HOLD_CO_OD                   ODCONBbits.ODCB3
#define L3_HOLD_CO_ANS                  ANSELBbits.ANSELB3
#define L3_HOLD_CO_SetHigh()            do { LATBbits.LATB3 = 1; } while(0)
#define L3_HOLD_CO_SetLow()             do { LATBbits.LATB3 = 0; } while(0)
#define L3_HOLD_CO_Toggle()             do { LATBbits.LATB3 = ~LATBbits.LATB3; } while(0)
#define L3_HOLD_CO_GetValue()           PORTBbits.RB3
#define L3_HOLD_CO_SetDigitalInput()    do { TRISBbits.TRISB3 = 1; } while(0)
#define L3_HOLD_CO_SetDigitalOutput()   do { TRISBbits.TRISB3 = 0; } while(0)
#define L3_HOLD_CO_SetPullup()          do { WPUBbits.WPUB3 = 1; } while(0)
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// get/set L4_HOLD_CO aliases
#define L4_HOLD_CO_TRIS                 TRISBbits.TRISB4
#define L4_HOLD_CO_LAT                  LATBbits.LATB4
#define L4_HOLD_CO_PORT                 PORTBbits.RB4
#define L4_HOLD_CO_WPU                  WPUBbits.WPUB4
#define L4_HOLD_CO_OD                   ODCONBbits.ODCB4
#define L4_HOLD_CO_ANS                  ANSELBbits.ANSELB4
#define L4_HOLD_CO_SetHigh()            do { LATBbits.LATB4 = 1; } while(0)
#define L4_HOLD_CO_SetLow()             do { LATBbits.LATB4 = 0; } while(0)
#define L4_HOLD_CO_Toggle()             do { LATBbits.LATB4 = ~LATBbits.LATB4; } while(0)
#define L4_HOLD_CO_GetValue()           PORTBbits.RB4
#define L4_HOLD_CO_SetDigitalInput()    do { TRISBbits.TRISB4 = 1; } while(0)
#define L4_HOLD_CO_SetDigitalOutput()   do { TRISBbits.TRISB4 = 0; } while(0)
#define L4_HOLD_CO_SetPullup()          do { WPUBbits.WPUB4 = 1; } while(0)
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// get/set L4_COIN_CONTROL aliases
#define L4_COIN_CONTROL_TRIS                 TRISBbits.TRISB5
#define L4_COIN_CONTROL_LAT                  LATBbits.LATB5
#define L4_COIN_CONTROL_PORT                 PORTBbits.RB5
#define L4_COIN_CONTROL_WPU                  WPUBbits.WPUB5
#define L4_COIN_CONTROL_OD                   ODCONBbits.ODCB5
#define L4_COIN_CONTROL_ANS                  ANSELBbits.ANSELB5
#define L4_COIN_CONTROL_SetHigh()            do { LATBbits.LATB5 = 1; } while(0)
#define L4_COIN_CONTROL_SetLow()             do { LATBbits.LATB5 = 0; } while(0)
#define L4_COIN_CONTROL_Toggle()             do { LATBbits.LATB5 = ~LATBbits.LATB5; } while(0)
#define L4_COIN_CONTROL_GetValue()           PORTBbits.RB5
#define L4_COIN_CONTROL_SetDigitalInput()    do { TRISBbits.TRISB5 = 1; } while(0)
#define L4_COIN_CONTROL_SetDigitalOutput()   do { TRISBbits.TRISB5 = 0; } while(0)
#define L4_COIN_CONTROL_SetPullup()          do { WPUBbits.WPUB5 = 1; } while(0)
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// get/set TEST_STATUS aliases
#define TEST_STATUS_TRIS                 TRISCbits.TRISC0
#define TEST_STATUS_LAT                  LATCbits.LATC0
#define TEST_STATUS_PORT                 PORTCbits.RC0
#define TEST_STATUS_WPU                  WPUCbits.WPUC0
#define TEST_STATUS_OD                   ODCONCbits.ODCC0
#define TEST_STATUS_ANS                  ANSELCbits.ANSELC0
#define TEST_STATUS_SetHigh()            do { LATCbits.LATC0 = 1; } while(0)
#define TEST_STATUS_SetLow()             do { LATCbits.LATC0 = 0; } while(0)
#define TEST_STATUS_Toggle()             do { LATCbits.LATC0 = ~LATCbits.LATC0; } while(0)
#define TEST_STATUS_GetValue()           PORTCbits.RC0
#define TEST_STATUS_SetDigitalInput()    do { TRISCbits.TRISC0 = 1; } while(0)
#define TEST_STATUS_SetDigitalOutput()   do { TRISCbits.TRISC0 = 0; } while(0)
#define TEST_STATUS_SetPullup()          do { WPUCbits.WPUC0 = 1; } while(0)
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// get/set IO_RC1 aliases
#define IO_RC1_TRIS                 TRISCbits.TRISC1
#define IO_RC1_LAT                  LATCbits.LATC1
#define IO_RC1_PORT                 PORTCbits.RC1
#define IO_RC1_WPU                  WPUCbits.WPUC1
#define IO_RC1_OD                   ODCONCbits.ODCC1
#define IO_RC1_ANS                  ANSELCbits.ANSELC1
#define IO_RC1_SetHigh()            do { LATCbits.LATC1 = 1; } while(0)
#define IO_RC1_SetLow()             do { LATCbits.LATC1 = 0; } while(0)
#define IO_RC1_Toggle()             do { LATCbits.LATC1 = ~LATCbits.LATC1; } while(0)
#define IO_RC1_GetValue()           PORTCbits.RC1
#define IO_RC1_SetDigitalInput()    do { TRISCbits.TRISC1 = 1; } while(0)
#define IO_RC1_SetDigitalOutput()   do { TRISCbits.TRISC1 = 0; } while(0)
#define IO_RC1_SetPullup()          do { WPUCbits.WPUC1 = 1; } while(0)
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// get/set IO_RC2 aliases
#define IO_RC2_TRIS                 TRISCbits.TRISC2
#define IO_RC2_LAT                  LATCbits.LATC2
#define IO_RC2_PORT                 PORTCbits.RC2
#define IO_RC2_WPU                  WPUCbits.WPUC2
#define IO_RC2_OD                   ODCONCbits.ODCC2
#define IO_RC2_ANS                  ANSELCbits.ANSELC2
#define IO_RC2_SetHigh()            do { LATCbits.LATC2 = 1; } while(0)
#define IO_RC2_SetLow()             do { LATCbits.LATC2 = 0; } while(0)
#define IO_RC2_Toggle()             do { LATCbits.LATC2 = ~LATCbits.LATC2; } while(0)
#define IO_RC2_GetValue()           PORTCbits.RC2
#define IO_RC2_SetDigitalInput()    do { TRISCbits.TRISC2 = 1; } while(0)
#define IO_RC2_SetDigitalOutput()   do { TRISCbits.TRISC2 = 0; } while(0)
#define IO_RC2_SetPullup()          do { WPUCbits.WPUC2 = 1; } while(0)
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// get/set IO_RC3 aliases
#define IO_RC3_TRIS                 TRISCbits.TRISC3
#define IO_RC3_LAT                  LATCbits.LATC3
#define IO_RC3_PORT                 PORTCbits.RC3
#define IO_RC3_WPU                  WPUCbits.WPUC3
#define IO_RC3_OD                   ODCONCbits.ODCC3
#define IO_RC3_ANS                  ANSELCbits.ANSELC3
#define IO_RC3_SetHigh()            do { LATCbits.LATC3 = 1; } while(0)
#define IO_RC3_SetLow()             do { LATCbits.LATC3 = 0; } while(0)
#define IO_RC3_Toggle()             do { LATCbits.LATC3 = ~LATCbits.LATC3; } while(0)
#define IO_RC3_GetValue()           PORTCbits.RC3
#define IO_RC3_SetDigitalInput()    do { TRISCbits.TRISC3 = 1; } while(0)
#define IO_RC3_SetDigitalOutput()   do { TRISCbits.TRISC3 = 0; } while(0)
#define IO_RC3_SetPullup()          do { WPUCbits.WPUC3 = 1; } while(0)
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// get/set IO_RC4 aliases
#define IO_RC4_TRIS                 TRISCbits.TRISC4
#define IO_RC4_LAT                  LATCbits.LATC4
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
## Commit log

2015-01-05 Initial commit of 1D Coin Controller project after verifying the hardware.
2015-01-05 Fix README.md formatting.
2015-01-05 More README.md formatting.
2015-01-05 Add document describing my Asterisk 13 setup on Ubuntu 14.04.
2015-01-05 Update links to patch Asterisk main/dsp.c.
2015-01-11 Update README.md to reflect that WE 32A and TeleService 4032C chassis are working with this design."
2015-01-11 Do not put the line on hold unless it is off hook. Putting the line on hold during coin/test operations when it is not already off-hook can lead to Asterisk interpreting the hold/unhold as a switch h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
2015-04-25 Remove outdated installation instructions
    These instructions have significant errors and omissions.
2015-04-25 Add missing sound files
2015-04-25 Add new instructions for Installing Asterisk 13 on Ubuntu
    These instructions were created while installing Asterisk and
    the payphone controller on a fresh Ubuntu 15.04 installation.
    During this process, I uncovered and several errors and
    omissions in the previous instructions.
    Installation on Ubuntu 14.04 should be similar.
2015-04-26 Update instructions for Google Voice
    Updated instructions for setting up Google Voice as a trunk.
2015-04-26 Update patch for easily application with patch utility
2015-06-02 Update AGI script to use standard Asterisk sound files
    Use sound files that come with Asterisk, rather than our own.
    To do this, three sound files are needed that do not come with
    the standard Asterisk distribution.
    cents-please.ulaw
    please-deposit.ulaw
    thank-you.ulaw
2015-07-07 Add expect scripts to interface with coin control hardware
    The 1D coin control hardware is connected to a Raspberry Pi via a
    serial port. The Raspberry Pi runs the ser2sock daemon to make the
    serial port available via telnet.
    These expect scripts run on the Asterisk server and talk via telnet
    to ser2sock running on the Raspberry Pi.
    https://github.com/nutechsoftware/ser2sock
2019-11-30 Update 1700/2200Hz coin tone detection for tip of Asterisk-13 branch.
2020-06-14 Firmware for the PIC18-based 1D Coin Controller
    Initial firmware.
2020-06-14 Update README.md for Issue 1 PCB.
2020-06-14 Add KiCAD files for Issue 1 PCB.
    WARNING: Do not fab this board as-is, the footprints for the 8P8C
    connectors are incorrect!
2020-06-14 Update schematic for Issue 1 PCB.
2020-06-29 Issue 2 schmatic and Layout
    Added polarity reversal detection to monitor answer supervision.
2020-06-29 Add LICENSE file.
2020-07-04 Update firmware for Issue 2.
    The Issue 2 PCB adds support for polarity-reversal detection
    on all four coin lines. This is useful for answer supervision
    detection.
    Hook status inputs are aggregated via an MCP-23008 i2c GPIO
    expander. The MCP-23008 generates an interrupt if any GPIO
    pin changes state, and the PIC microcontroller updates the
2020-07-04 Add pulse-counting logic.
2020-07-05 Support pulse dialing across multiple lines.
2020-07-05 Add photo of the Issue 2 PCB.
2020-07-12 Change coin line functions to be 0-based.
2020-07-12 Change INT2 interrupt from active high to active low.
2020-07-12 Always hold CO lines during coin/test operations.
2022-07-24 Major firmware overhaul.
    * Update for MPLAB X v6.00
    * Swap PIC18F4550 for the newer PIC18F47Q84, removing USB.
    * Remove the MCP23008 i2c I/O expander, use "Interrupt on Change"
    pins directly.
2022-08-06 Resolve Issue #1: typographical error on board
2022-08-07 Issue 3:
    * Remove barrel jack, replace with 4-position terminal block with
    provision for +/- 130VDC input in case the user already has an
    appropriate power supply and does not want the on-board
    DC-DC converter. Note: 130V DC-DC converter PS2, relay
    K8, C14, D10, and R16 must be omitted during assembly.
    * Add bi-color LEDs for line status.
2024-03-24 Issue 4: Switch from PIC to AVR128DA28 MCU.
    * The AVR128DA28 is supported by the Arduino IDE.
    * Simpler UPDI programming.
    * Update to KiCAD 8.0.1
    * Fix footprint outline for IA1224S DC-DC converter.
    * Add initial Arduino firmware for AVR128DA28 MCU.
    * Move Earth Ground hole.
